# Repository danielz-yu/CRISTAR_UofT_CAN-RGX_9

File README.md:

# CRISTAR UofT | CAN-RGX 9

CRISTAR aims to investigate laser-induced crystallization under both microgravity and hypergravity conditions. Our project will use a compact laser cavitation system to generate crystals under different gravity environments. We will then compare the size, structure and purity of the resulting lysozyme crystals to determine how gravity influences morphology and structural characteristics. This work aims to reduce the cost of microgravity-grown crystals by leveraging short-duration suborbital flights. 

#

**Team Members:**
- Alexander Wainwright
- Khaled Madhoun
- Elias Barsa
- Gabriel Caribé
- Syeda Mahdia
- Lauren Altomare
- Daniel Yu
- Natalie Djuric

[Canadian Reduced Gravity Experiment Design Challenge | 2025-2026 Teams](https://www.seds.ca/can-rgx/#current)

#

### Setup and Run

Main GUI script: `cristar_gui.py`  
Required dependencies: `requirements.txt`

### 1. Local Setup

```bash
python3 -m venv .venv
source .venv/bin/activate
pip install --upgrade pip
pip install -r requirements.txt
```

### 2. Running the Main GUI

Aliases set up on the Raspberry Pi
```bash
connections
gui
connections
start
```

If these aliases are unavailable in a non-interactive shell, run the script directly:
```bash
/home/cristar/Documents/GUI_Development.venv/bin/python /home/cristar/Documents/GUI_Development/cristar_gui.py
```

### 3. Testing Scripts

The `testing/` folder contains helper/testing scripts.
```bash
python3 Connections.py
```

### 4. Raspberry Pi Quick Access

- Pi hostname/user: `cristar@cristar.local`
- Pi password: `cristar2026`
- Alias available on the Pi setup: `gui` (runs the main GUI)
```bash
ssh cristar@cristar.local
gui
```

### 5. Remote GUI from a Second Computer (SSH + Ethernet/Wi-Fi + X11)

If running the GUI remotely from another computer (for example over Ethernet), install XQuartz and launch with X11 forwarding:
```bash
open -a XQuartz
export DISPLAY=:0
ssh -Y -o ForwardX11=yes -o ForwardX11Trusted=yes cristar@cristar.local
gui
```

#

<br>

<p align="center">
  </a>
  &nbsp;&nbsp;&nbsp;&nbsp;
  </a>
</p>

<br>

<div align="center">
    
</div>

<br>

<div align="center">
    
</div>

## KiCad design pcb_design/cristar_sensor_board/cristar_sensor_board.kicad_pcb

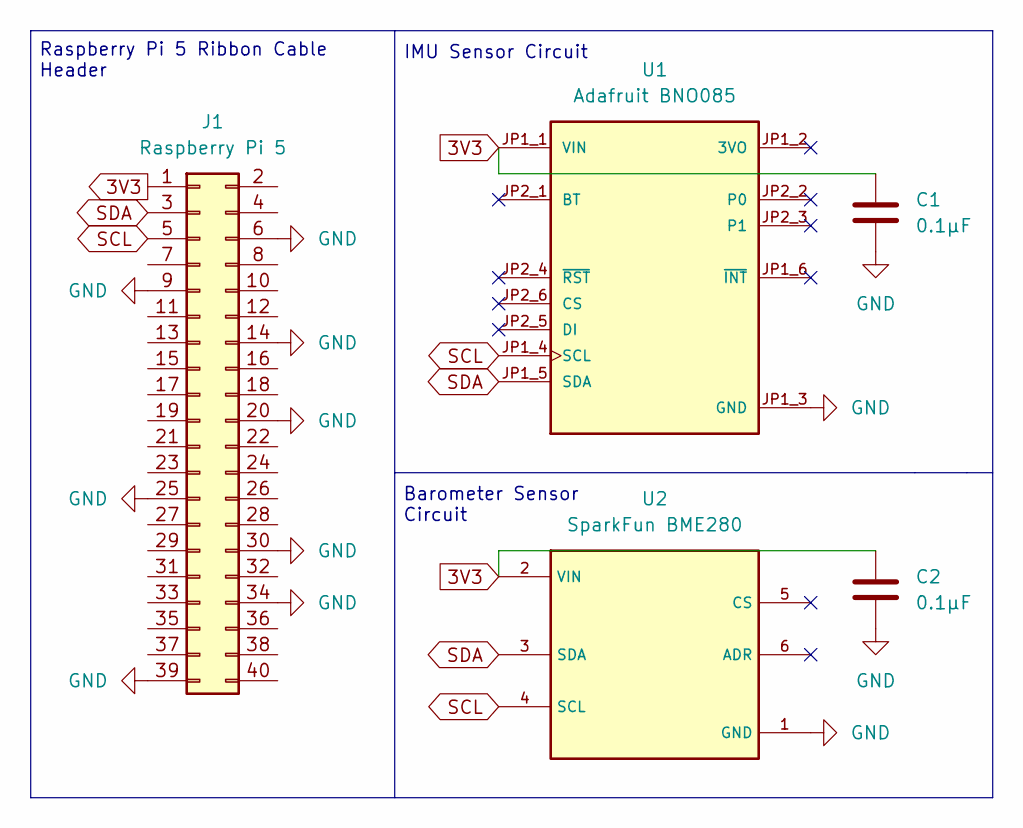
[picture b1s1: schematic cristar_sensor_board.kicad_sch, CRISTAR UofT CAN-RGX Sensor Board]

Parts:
C1, C2: 0.1µF; C_0805_2012Metric_Pad1.18x1.45mm_HandSolder
J1: Raspberry Pi 5; 3M_D3432-6302-AR
U1: Adafruit BNO085; Adafruit_BNO085; PARTREV 2021-03-16
U2: SparkFun BME280

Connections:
3V3: C1.1, C2.1, J1.1, U1.JP1_1 (VIN), U2.2 (VIN)
GND: C1.2, C2.2, J1.6, J1.9, J1.14, J1.20, J1.25, J1.30, J1.34, J1.39, U1.JP1_3 (GND), U2.1 (GND)
SCL: J1.5, U1.JP1_4 (SCL), U2.4 (SCL)
SDA: J1.3, U1.JP1_5 (SDA), U2.3 (SDA)

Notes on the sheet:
Raspberry Pi 5 Ribbon Cable Header
IMU Sensor Circuit
Barometer Sensor Circuit

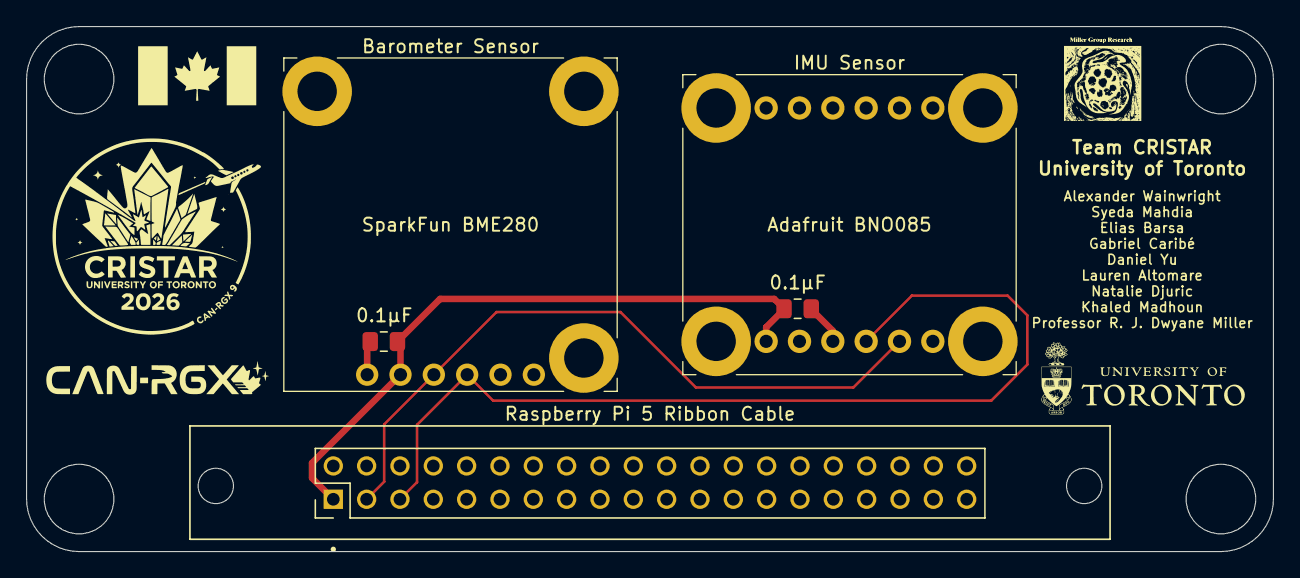
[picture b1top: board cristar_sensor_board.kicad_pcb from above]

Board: 2 copper layers, 95.0 x 40.0 mm, 5 parts (0 on the bottom side), 4 nets.

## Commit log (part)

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2026-01-21 Update project title in README
2026-01-24 Initial readme commit
2026-01-24 Update README with Canadian RGX Challenge details
    Added links and logos for the Canadian Reduced Gravity Experiment Design Challenge and associated teams.
2026-01-27 Added the GUI file to the project
2026-03-06 Initial sensor prototype code
2026-03-06 Adding requirements.txt
2026-03-06 Adding virtual environment to git tracking
2026-03-06 Updating gitignore
2026-03-06 Stop tracking virtual environment (.venv)
2026-03-06 Adding test for X11 fowarding
2026-03-07 Fixing I2C in sensors.py, libraries required in requirements.txt, and adding basic sensor outputs for main GUI
2026-03-07 Organizing test files
2026-03-07 Documenting RaspPi5 GPIO pin connections
2026-03-07 Formatting README
2026-03-07 Adding setup instructions
2026-03-07 Revise README sections for improved clarity
    Updated headings and formatting for consistency and clarity.
2026-03-23 Adding PCB files and renders
2026-03-23 Fix spelling of Gabriel Caribé's name
2026-03-23 PCB update
2026-03-23 Adding new PCB render
